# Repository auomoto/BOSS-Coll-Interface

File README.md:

# BOSS-Coll-Interface
 Interface board between specMech and collimator motors
This board brings in 12VDC and serial data from the specMech box.

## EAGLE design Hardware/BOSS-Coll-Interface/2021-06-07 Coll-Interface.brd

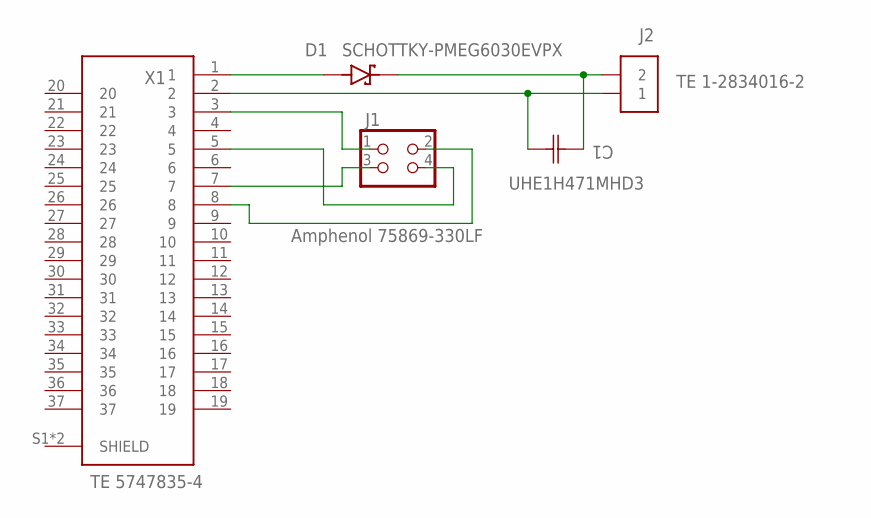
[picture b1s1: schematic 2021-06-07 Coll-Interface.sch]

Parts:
C1: UHE1H471MHD3; U1-EE_NCH
D1: SCHOTTKY-PMEG6030EVPX; DIO_PMEG6030EVPX
J1: Amphenol 75869-330LF; 2X02-SHROUD
J2: TE 1-2834016-2; TE_1-2834016-2
X1: TE 5747835-4; TE_5747835-4

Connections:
+24V-FROM-SPECMECH: D1.2 (A), X1.1
+24V-TO-ROBOCLAW: C1.1, D1.1 (K), J2.2.1 (2), J2.2.2 (2)
GND-ROBOCLAW: C1.2, J2.1.1 (1), J2.1.2 (1), X1.2
GND-SPECMECH: J1.4, X1.5
ROBO-RX: J1.1, X1.3
ROBO-TX: J1.3, X1.7
VCC-SPECMECH: J1.2, X1.8

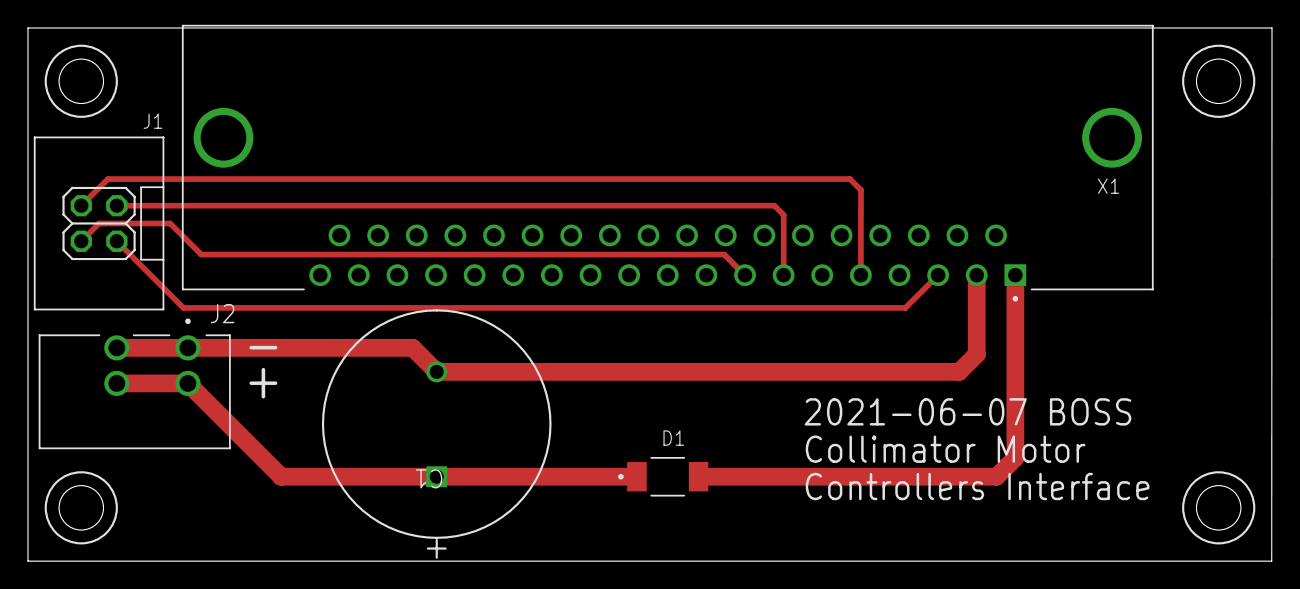
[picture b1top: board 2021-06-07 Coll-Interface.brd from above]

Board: 2 copper layers, 88.9 x 38.1 mm, 5 parts (0 on the bottom side), 7 nets.

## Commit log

2021-02-21 Created Eagle project
2021-05-03 Made a copy to submit to manufacturing
2021-05-04 Made a 2021-05-03 copy, to manufacture (2021-04-27 needed a change)
2021-05-27 Changed hole size on capacitor leads
2021-07-24 Opened up the holes for the capacitor
